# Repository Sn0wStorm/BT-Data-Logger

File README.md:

# BT-Data-Logger
A Project for the Microcontroller Seminar

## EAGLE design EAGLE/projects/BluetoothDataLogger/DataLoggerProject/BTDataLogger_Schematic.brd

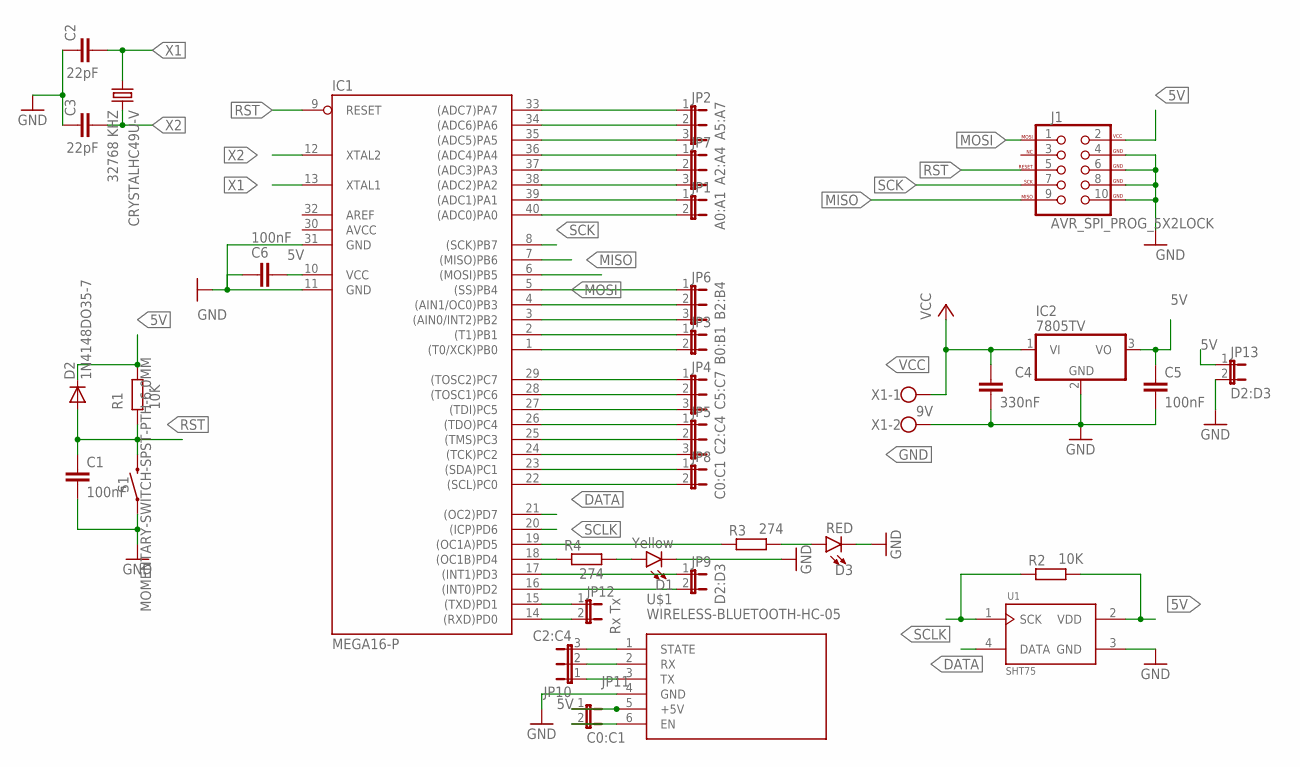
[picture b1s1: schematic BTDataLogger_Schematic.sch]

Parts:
C1, C5, C6: 100nF; C025-024X044
C2, C3: 22pF; C025-024X044
C4: 330nF; C5B3
CRYSTALHC49U-V: 32768 KHZ; HC49U-V
D1: Yellow; LED-0603
D2: 1N4148DO35-7; DO35-7
D3: RED; LED-0603
IC1: MEGA16-P; DIL40
IC2: 7805TV; TO220V
J1: AVR_SPI_PROG_5X2LOCK; 2X5-SHROUDED_LOCK
JP1: A0:A1; JP1
JP2: A5:A7; JP2
JP3: B0:B1; JP1
JP4: C5:C7; JP2
JP5, JP10: C2:C4; JP2
JP6: B2:B4; JP2
JP7: A2:A4; JP2
JP8, JP11: C0:C1; JP1
JP9, JP13: D2:D3; JP1
JP12: Rx Tx; JP1
R2: 10K; 0207/10
R3, R4: 274; 0207/10
S1: MOMENTARY-SWITCH-SPST-PTH-6.0MM; TACTILE_SWITCH_PTH_6.0MM
U1: SHT75; SIP310W46P127L508H1350Q4P
U$1: WIRELESS-BLUETOOTH-HC-05
X1: 9V; W237-102

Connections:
5V: C5.1, C6.1, D2.C, IC1.10 (VCC), IC2.3 (VO), J1.2 (VCC), JP11.1, JP13.1, R2.2, U1.2 (VDD), U$1.5 (+5V)
AVCC: IC1.30 (AVCC)
DATA: IC1.21 ((OC2)PD7), U1.4 (DATA)
GND: C1.2, C2.1, C3.1, C4.2, C5.2, C6.2, D1.C, D3.C, IC1.11 (GND), IC1.31 (GND), IC2.2 (GND), J1.4 (GND), J1.6 (GND), J1.8 (GND), J1.10 (GND), JP13.2, S1.1, U1.3 (GND), U$1.4 (GND), X1.2
MISO: IC1.7 ((MISO)PB6), J1.9 (MISO)
MOSI: IC1.6 ((MOSI)PB5), J1.1 (MOSI)
unnamed: JP10.3, U$1.1 (STATE)
unnamed: JP10.2, U$1.2 (RX)
unnamed: IC1.18 ((OC1B)PD4), R4.1
unnamed: D1.A, R4.2
unnamed: D3.A, R3.2
unnamed: IC1.19 ((OC1A)PD5), R3.1
unnamed: IC1.33 ((ADC7)PA7), JP2.1
unnamed: IC1.34 ((ADC6)PA6), JP2.2
unnamed: IC1.35 ((ADC5)PA5), JP2.3
unnamed: IC1.36 ((ADC4)PA4), JP7.1
unnamed: IC1.37 ((ADC3)PA3), JP7.2
unnamed: IC1.38 ((ADC2)PA2), JP7.3
unnamed: IC1.5 ((SS)PB4), JP6.1
unnamed: IC1.4 ((AIN1/OC0)PB3), JP6.2
unnamed: IC1.3 ((AIN0/INT2)PB2), JP6.3
unnamed: IC1.29 ((TOSC2)PC7), JP4.1
unnamed: IC1.28 ((TOSC1)PC6), JP4.2
unnamed: IC1.27 ((TDI)PC5), JP4.3
unnamed: IC1.26 ((TDO)PC4), JP5.1
unnamed: IC1.25 ((TMS)PC3), JP5.2
unnamed: IC1.24 ((TCK)PC2), JP5.3
unnamed: IC1.39 ((ADC1)PA1), JP1.1
unnamed: IC1.40 ((ADC0)PA0), JP1.2
unnamed: IC1.2 ((T1)PB1), JP3.1
unnamed: IC1.1 ((T0/XCK)PB0), JP3.2
unnamed: IC1.23 ((SDA)PC1), JP8.1
unnamed: IC1.22 ((SCL)PC0), JP8.2
unnamed: IC1.17 ((INT1)PD3), JP9.1
unnamed: IC1.16 ((INT0)PD2), JP9.2
unnamed: JP10.1, U$1.3 (TX)
unnamed: JP11.2, U$1.6 (EN)
unnamed: IC1.15 ((TXD)PD1), JP12.1
unnamed: IC1.14 ((RXD)PD0), JP12.2
RST: C1.1, D2.A, IC1.9 (RESET), J1.5 (RESET), S1.3 (2)
SCK: IC1.8 ((SCK)PB7), J1.7 (SCK)
SCLK: IC1.20 ((ICP)PD6), R2.1, U1.1 (SCK)
VCC: C4.1, IC2.1 (VI), X1.1
X1: C2.2, CRYSTALHC49U-V.1, IC1.13 (XTAL1)
X2: C3.2, CRYSTALHC49U-V.2, IC1.12 (XTAL2)

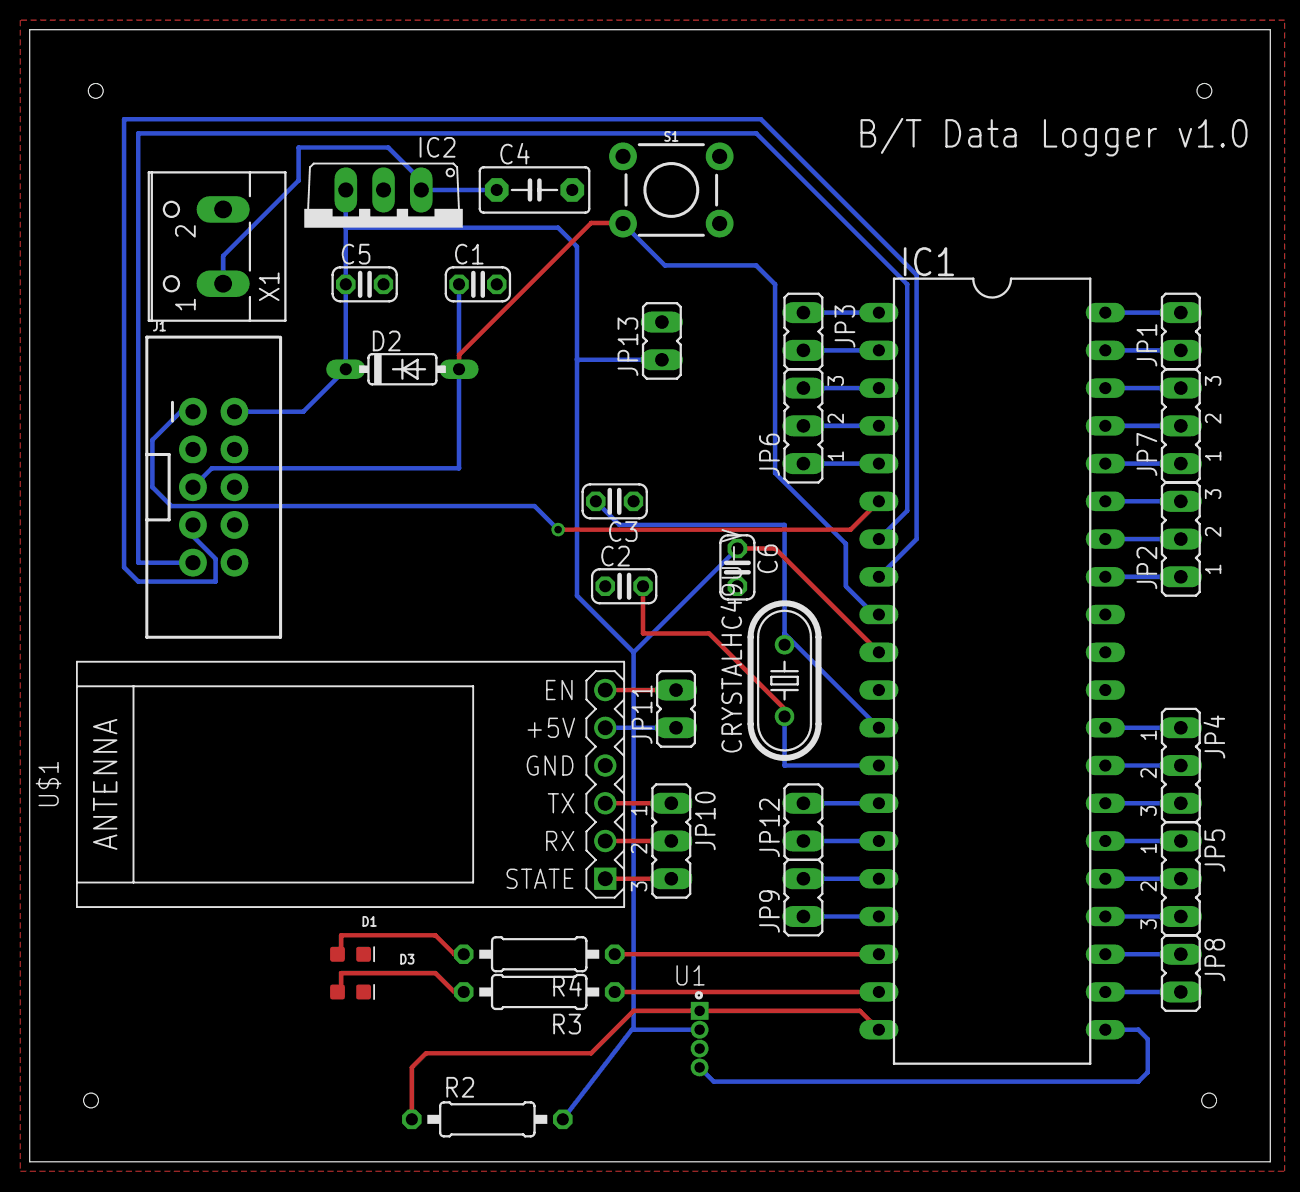
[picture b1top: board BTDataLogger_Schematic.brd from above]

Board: 2 copper layers, 83.5 x 76.2 mm, 33 parts (0 on the bottom side), 44 nets.

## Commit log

2018-11-22 Simple USART Test
2018-11-22 Added the eagle schematic and PCB layout file to the Project
2018-11-26 Use a String to send data
2019-01-15 Some Comments and new Delay
2019-01-15 Start SHT Sensor reading
2019-01-16 Continued Sensor Protocol
2019-01-17 Forgot to enable Pull Up resistor again
2019-01-24 Added loop to measuring
2019-02-01 Added reading and sending of Humidity
2019-02-08 Fixes to the Transmittion of Humidity
    Use SRam to store the data
2019-02-10 Added the Android App

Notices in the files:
parts and their libraries:
SparkFun-LED: Licensing: Creative Commons ShareAlike 4.0 International - https://creativecommons.org/licenses/by-sa/4.0
diy-modules: Released under the Creative Commons Attribution 4.0 International License: http://creativecommons.org/licenses/by/4.0
